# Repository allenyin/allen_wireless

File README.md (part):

**Wireless Neural Recording System**

* [Overview](#Overview)
* [Hardware](#Hardware)
	* [Steps to convert old KiCad design files](#convertKiCad)
	* [Bridge](#Bridge-hw)
	* [Headstages](#headstages)
* [Firmware](#Firmware)
	* [Dependency](#Firmware-dependency)
	* [Bridge](#Bridge-fw)
	* [RHA-headstage](#RHA-fw)
	* [RHD-headstage](#RHD-fw)
		* [Firmware versions](#firmware-versions)
		* [JTAG testing](#JTAG-testing)
		* [Utility Programs](#Utility-programs)
* [Client Software](#gtkclient)
	* [Dependency](#gtkclient-dependency)
	* [Compilation](#gtkclient-compile)
    * [Running gtkclient](#running-gtkclient)
        * [RHA-headstage gtkclient](#RHAgtkclient)
        * [RHD-headstage gtkclient](#RHDgtkclient)
        * [Spike sorting](#SpikeSorting)
        * [Saving recordings](#SavingRecordings)
        * [Test recording](#TestRecording)
        * [Configuration files](#gtkclientConfigurations)
	* [TODO/possible improvements](#gtkclient-TODO)
* [Quick Start](#quickstart)

## <a name="Overview">Overview</a>
This project is modified from the multi-branch of the wireless neural recording system of the [myopen project](https://github.com/tlh24/myopen/tree/multi) by Tim Hanson.

As summarized in Hanson's [thesis](http://m8ta.com/tim/dissertation.pdf), the original system 

>consists of digitizing headstages, receiver/ethernet bridge, and PC client software. Each headstage has 4 32-channel Intan analog amplifiers, and ADCs to digitize the amplified signals. The amplifiers are connected to an onboard Blackfin DSP BF532 which performs automatic gain control, LMS adaptive noise cancellation, 8 poles of high and lowpass filtering, two templates comparison per channel, data compression, and pipelined radio control. The radio onboard transmits 1.3Mbps full filtered analog trace of four channels and threshold/template match for two units on all 128 channels. This is interleaved with 83kbps reception,which allows the client to edit parameters on the transceiver. The radio protocol allows any memory location to be changed on the headstage (specifically the blackfin), and the headstage streams can stream from any location in memory, with the memory address set by the PC client.

[32-channel Intan analog amplifiers](http://intantech.com/products_RHA2000.html)

[Blackin DSP BF532](http://www.analog.com/en/products/processors-dsp/blackfin/adsp-bf532.html)

The bridge, which is based around [Blackfin DSP BF537](http://www.analog.com/en/products/processors-dsp/blackfin/adsp-bf537.html), collects the wirelessly transmitted data from the headstages and send them to the PC client through ethernet.

<a name="figure_overview">*System overview, from Hanson's [thesis](http://m8ta.com/tim/dissertation.pdf)*</a>

This project modified the wireless headstage by replacing each of the 4 RHA2132 amplifiers, ADCs, and power converter chips with a single [32-channel RHD2132 digitizing amplifier](http://intantech.com/products_RHD2000.html). This is to reduce the power consumption and total area of the final PCB (by about 1/3). In terms of the figure above, this is equivalent of replacing the `G=200 and 32:1 multiplexer`, `ADC` and `LDO` components in the `Digitizing headstage` blocks by one component. 

In the rest of this document, the original headstages will be refered to as **RHA-headstage**, while the new design will be referred to as **RHD-headstage**. The client software will be referred to as **gtkclient**.

This document will describe:

* The overall hardware architecture of the headstages.
* Usage and setup for the bridge, headstage, and the PC client software.
* The different firmware versions used to develop and test the RHD-headstage.
* Debugging tools.

For technical details on the implementation, development, and troubleshooting of the firmware, see Tim's thesis, and the following development notes:

1. [Wireless Headstage: Blackfin BF532 headstage firmware setup](http://allenyin.github.io/reading_list/2016/01/BlackfinSetup)
2. [Wireless Headstage: Blackfin BF532 communication with Intan RHD2132 via SPI simulation via SPORT](http://allenyin.github.io/reading_list/2015/12/Blackfin-Intan-SPORT)
3. [Wireless Headstage: AGC with Blackfin BF532 and Intan RHD2132](http://allenyin.github.io/reading_list/2015/12/WirelessAGC)
4. [Wireless Headstage: Least-Mean Squared (LMS) adaptive noise cancellation](http://allenyin.github.io/reading_list/2016/01/BlackfinLMS)
5. [Wireless Headstage: Implementing direct-form I biquad IIR filters](http://allenyin.github.io/reading_list/2016/01/DirectFormI-IIR-butterworth-filters)
6. [Wireless Headstage: Generate oscillations by setting IIR coefficients](http://allenyin.github.io/reading_list/2016/01/IIRoscillator)
7. [Spike sorting via PCA and spike detection with SAA](http://allenyin.github.io/reading_list/2016/01/BlackfinSpikeSorting)
8. [Wireless Headstage: Radio transmission protocol between headstage and gtkclient](http://allenyin.github.io/reading_list/2016/01/BlackfinRadioTrans)
9. [Wireless Headstage: gtkclient notes](http://allenyin.github.io/reading_list/2016/01/gtkclient)

This repository contains the following folders:

* `bridge_hardware`: Ported from myopen's [stage10](https://github.com/tlh24/myopen/tree/master/emg_dsp/stage10). Components  stored in `bridge_library/`. Footprint archived to `bridge_library.pretty/` to use with newer version of `kicad (Version:0.201506030104+5696~23~ubuntu14.04.1-product,release build)`.

* `headstage_hardware`: Ported from myopen's [stage9](https://github.com/tlh24/myopen/tree/master/emg_dsp/stage9). Components stored in `headstage_library/`. Footprint archived to `headstage_library.pretty/` to use with newer version of kicad.

* `headstage2_hardware`: Modified from myopen's [stage9](https://github.com/tlh24/myopen/tree/master/emg_dsp/stage9). Uses 4xRHD2132 amplifiers rather than 4xRHA2132 amplifiers front-end. Eliminated separate ADCs and analog power-supply components.

* `myopen_multi`: Firmware and gtkclient software, which includes:
    * `bridge_firmware`: Same as myopen's [firmware_stage7](https://github.com/tlh24/myopen/tree/mutli/firmware_stage7).
    * `headstage_firmware`: Firmware for RHA-headstage. Port from myopen's [firmware_stage9_tmpl](https://github.com/tlh24/myopen/tree/multi/firmware_stage9_tmpl). Uses templates matching to transmit spike timings from the headstage.
    * `headstage2_firmware`: Firmware, development and debugging files for RHD-headstage.
    * `gtkclient_multi`: gtkclient source code adapted from myopen. Makefile modified to compile on Ubuntu14.04 and to support working with RHD-headstage's firmware.
    * `flasher`: Code used to write to the flash memories of the bridge and headstage through the parallel port.
    * `common_bfin`: Code common to all firmware and gtkclient.
    * `common_host`: Code common to the bridge firmware and gtkclient.
    * `algs`: Utilities need by gtkclient.
    
---
## <a name="Hardware">Hardware</a>

## <a name="convertKiCad">Steps to convert old KiCad design files</a>
The bridge and RHA-headstage PCB were designed with Tim's [kicadocaml](https://github.com/tlh24/kicadocaml), a variant of the opensource [KiCad](http://kicad-pcb.org/) PCB cad program. The design files were ported to KiCad, however the recent changes in KiCad's EESchema introduces some problems in using projects created with older version out of the box. Those impacts include:

0. Updated device library. The new device library footprints are smaller, this can cause older schematics to be displayed with broken connections. Solution: follow the procedures outlined [here](https://lists.launchpad.net/kicad-developers/msg17639.html) to use the rescue-lib.
0. Saving the old .brd files will convert them to .kicad_pcb. Subsequent openning of the board files will then result in parse errors and no board. Solution: Never save!!! (have not yet found a good solution).

In general, the KiCad files in `bridge_hardware/` and `headstage_hardware/` are for reference only, no save/modification should be needed.

The following steps were used to convert the old project files (example using `headstage_hardware/`):

0. Extract stage9 from `/emg_dsp`.
0. Create component and footprint library folders. `cd headstage_hardware; mkdir headstage_library headstage_library.pretty`
0. Open the schematic file, press OK for the rescue components dialog. Copy the cached component to our newly created library: `cp stage9-cache.lib headstage_library/headstage.lib`
0. Go to *Preferences*->*Component Libraries* and add headstage as an active library.
0. Ctrl-E on any of the component to open library editor. Set active library to be *headstage* and save component.
0. Close schematic and open again. Now editing any of the components in the library editor should show the active library as *headstage.lib*
0.  **Important! When closing the schematic, do not click on save!**
0. Open the .brd file, click ok on the resulting dialog.
0. Ctrl-E on any of the footprint to open the footprint editor. Click on *Create new library and save footprint* from the menu bar, and select the *headstage_library.pretty* folder to store the new library.
0. Go to *Preferences*->*Footprint libraries Wizard*->*Files on my computer* and select the *headstage_library.pretty* folder. This will add that directory to the footpring libraries available in this project. Make sure to select avaliable to project only.
0. *Select active library* in the footprint editor and make it *headstage_library.pretty*.
0. Close footprint editor and go back to the board. Go to *file*->*Archive Footprints*->*Create footprint archive* and select *headstage_library.pretty* as the library. Click yes to replace library. Now *headstage_library.pretty/* contains all the footprint used in the board as .mod files.
0. Make sure when footprint editor is opened, the active library is set correctly to the one we just created.
0. Again remeber to **NOT save the board file!!**
0. Open the schematic file and run Cvpcb to associate the components and the footprints in our own custom libraries. It's possible that a footprint is found in multiple libraries, chose to associate with the ones in *headstage*.

## <a name="Bridge-hw">Bridge</a>
As illustrated by the [Receiver block in the system overview](#figure_overview), the bridge mainly consists of three antenna-2.4GHz radio pairs for wireless communication, Blackfin DSP for processing, Ethernet/MAC chip for communication with gtkclient, and DAC (typo of DAC in Tim's thesis) for outputting received neural signals as audio.

In addition to wireless communication with the headstages, the bridge is also needed to program and debug the headstages.

<a name="bridge_labeled">*Bridge Board* </a>

In the above image:

A. Power switch.

B. USB power cable. 

C. Ethernet cable. Each operating headstage requires a bridge, requiring the PC on which gtkclient operates on to be connected to multiple bridges. Therefore, the ethernet port of the bridges and the client PC should all connect to the same switch or router.

D. Audio jack. When gtkclient is running, connecting the bridge to an audio device allows the user to hear the the 4 selected channels in gtkclient.

E. Blackfin BF537 DSP processor.

F. JTAG header pins for debugging the bridge. The pin missing on the top row ensures correct orientation of the JTAG in-circuit emulator (ICE).

G. Header pins for writing firmware to the bridge's flash memory. See [bridge flashing instructions](#Bridge-fw).

H. Indicator LED lights. After power on, these LEDs would fluctuate. Normal operation is indicated by the LEDs lit up in the image lighting up. Except for the bottom most one, which should be blinking periodically.

I. Header pins for writing firmware to the headstage's flash memory. See [RHA-flashing instructions](#RHA-fw) and [RHD-flashing instructions](#RHD-fw).

J. Omnetics connector for writing firmware to the headstage's flash memory. The signals applied to the column of header pins above it are applied to the headstage through this connection to the corresponding omnetics connector on the headstage.

K. JTAG header pins for debugging the headstage. The pin missing on the left column ensures correct orientation of JTAG ICE. See [RHD firmware testing](#JTAG-testing).

L. Omnetics connector for JTAG debugging the headstage. The signals applied to the JTAG header pins are passed to the headstage through this connection.

M. 2.4GHz Nordic radio and antenna pairs. Having three antenna allow for spatial reception diversity and enable better wireless signal quality.

**Parallel Port Flash Cable**

A 25-pins [IBM PC-comptabile parallel port](https://en.wikipedia.org/wiki/Parallel_port#Pinouts) cable is modified to use for the flashing process, see [firmware section](#Firmware) for instructions.  The unmodified end of the DB25 cable is connected to the parallel port, while the modified end connects to the 7-pin header connectors on the bridge, labeled G and I above.

The flash cable on one end needs to be modified as shown below:

<a name="flash_cable">*Flash Cable Schematic*</a>

The left box shows the relevant pins on the unmodified DB25 connector, the right box shows the corresponding header pins on the bridge. There needs to be a `33pF` capacitor connecting `pin23` and `pin4` of the parallel cable. `pin5` of the cable needs to connect to the base of an NPN transistor, whose emmiter is connected to ground via either `pin23` or `pin24`, while the collector goes to `pin7` of the bridge headers.

Specifically, the parallel port to SPI correspondence is:

* `pin2` = `_CS` -- chip select of the SPI flash memory.
* `pin13` = `SO` -- the input of the parallel port is connected to the output (SO) of the flash memory.
* `pin3` = `SI` -- the output of the parallel port is connected to the input (SI) of the flash memory.
* `pin4` = `SCLK` -- serial clock (SCLK) of the flash memory.

`pin5` is not part of the 4-line SPI interface, but it is used to allow the line-driver onboard the bridge to select the flash memory to use the SPI bus. This is necessary since the SPI bus on the Blackfins of both the bridge and headstage is shared between the flash memory and the radio chip.

The modified flash cable will include the capacitor and the NPN transistor. The polarity of the 7-pin connector can be figured out by probing to see which pin is grounded onboard the bridge.

## <a name="headstages">Headstages</a>

In image below, the fully assembled RHA-headstage is on the left. The RHD-headstage is on the right.

<a name="headstages_labeled">*Headstage PCBs*</a>

Labeled in the image are the connectors the headstages can make:

A. RHA-headstage Omnetics connectors to electrodes. Each of the four connectors has two rows of 20 pins each. The leftmost and rightmost pins of each row are guide posts and connect no signals. The second leftmost and the second rightmost pins of each row are the reference electrodes.

B. RHA-headstage power connection to 3.7V battery.

C. RHA-headstage Omnetics connector for flashing memory. The JTAG debugging connector is on the back side of the board at the same location.

D. RHD-headstage Omnetics connectors to electrodes. Exactly the same as the RHA-headstage.

E. RHD-headstage power connection to 3.7V battery. Connection not installed in the pictre.

F. RHD-headstage Omnetics connector for flashing memory. The JTAG debugging connector is on the back side of the board at the same location.

The bottom half of both headstages are the `digitizing headstages` block in the [System overview diagram](#figure_overview), which is where the headstages differ hardware-wise. The top halves are the `transceiver block` and are identical.

While the electrodes for both headstages are identical, the electrode-to-amplifier connections are different. Below are the electrode-to-channel mapping for each headstage, containing only the 32 signal-carrying electrodes of the connector (excluding the guide posts). Note that each amplifier is connected to one group of 32 electrodes.

*RHA-headstage electrode-to-channel mapping, ordered from left-to-right*

top-row|31|30|29|28|27|26|25|24|23|22|21|20|19|18|17|16|
-------|---|---|---|---|---|---|---|---|---|---|---|---|---|---|---|---|
bot-row|15|14|13|12|11|10| 9| 8| 7| 6| 5| 4| 3| 2| 1| 0|

*RHD-headstage electrode-to-channel mapping, ordered from left-to-right*

top-row|23|22|21|20|19|18|17|16|15|14|13|12|11|10|9|8|
-------|---|---|---|---|---|---|---|---|---|---|---|---|---|---|---|---|
bot-row|24|25|26|27|28|29|30|31|0|1|2|3|4|5|6|7|

## <a name="Firmware">Firmware</a>
The firmware is written in a combination of C and Blackfin assembly language. While Analog Devices (ADI) provides its own software development toolchains, it requires purchasing a pretty expensive license (though it comes with a lot more support). For the myopen and this project, the open source gnu gcc blackfin toolchain is used. Further, all development was done on debian based OS. The Makefiles in this repository are tested only in Ubuntu 14.04. Minor adjustments might be needed to work on other debian-based OS.

## <a name="Firmware-dependency">Dependency</a>

Compiling the firmware requires the [Blackfin Toolchain in Linux for Bare Metal](https://blackfin.uclinux.org/doku.php?id=toolchain:installing). For debian-based linux OS:

* Download the latest version, as of June, 2015, it's `blackfin-toolchain-elf-gcc-4.3-2014R1-RC2.x86_64.tar.bz2`
* Extract and move to `/opt`
* Add path to `/opt/uClinux/bfin-elf/bin` to the `PATH` variable through `.bashrc`

Two must-have references to understand Blackfin architecture:

* [ADSP-BF5xx/ADSP-BF60x Blackfin Processor Programming Reference](http://www.analog.com/media/en/dsp-documentation/processor-manuals/Blackfin_pgr_rev2.2.pdf), describes all assembly commands and options.
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
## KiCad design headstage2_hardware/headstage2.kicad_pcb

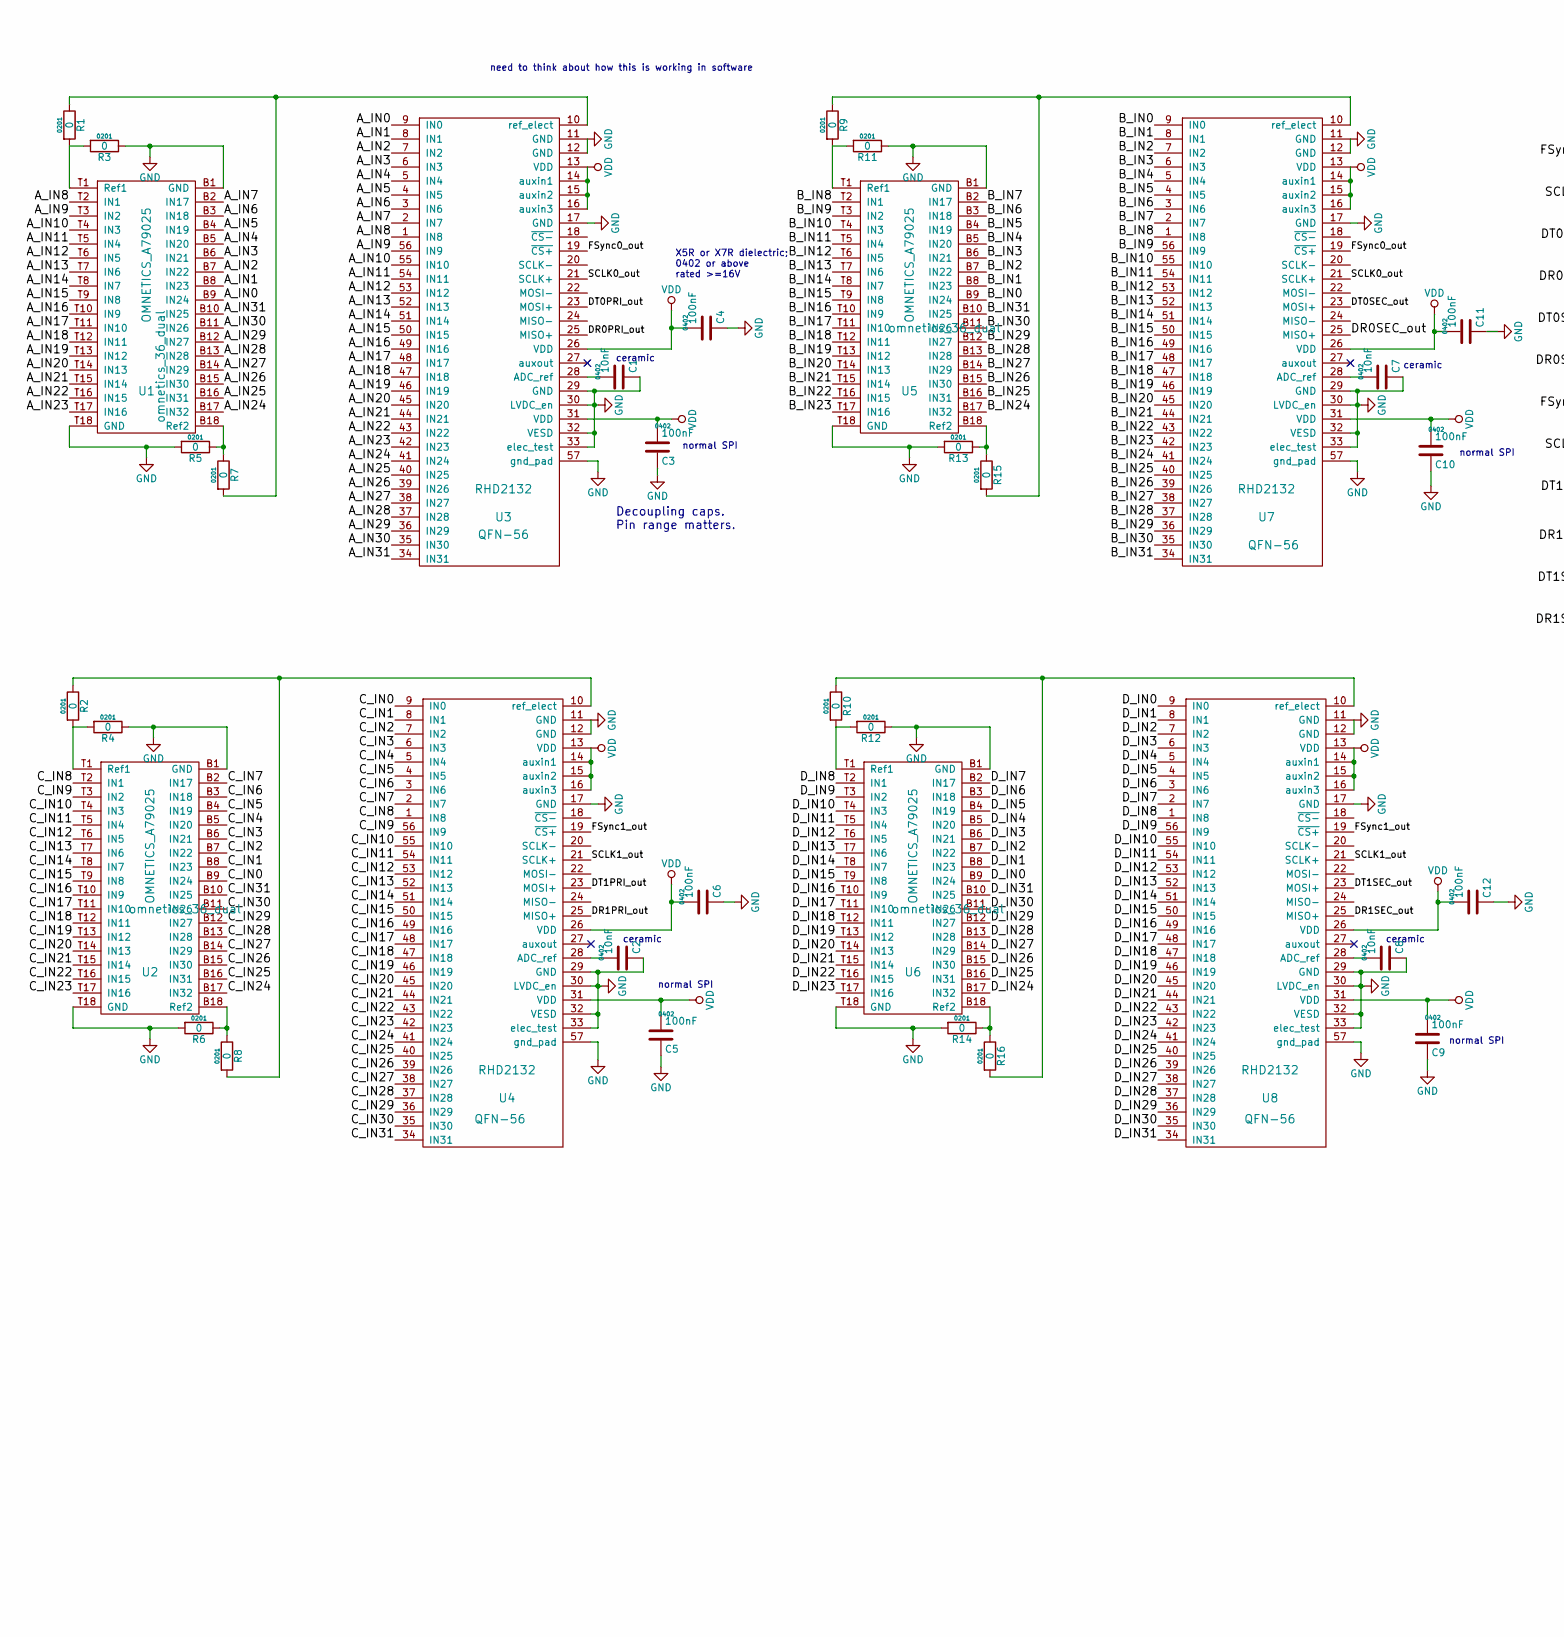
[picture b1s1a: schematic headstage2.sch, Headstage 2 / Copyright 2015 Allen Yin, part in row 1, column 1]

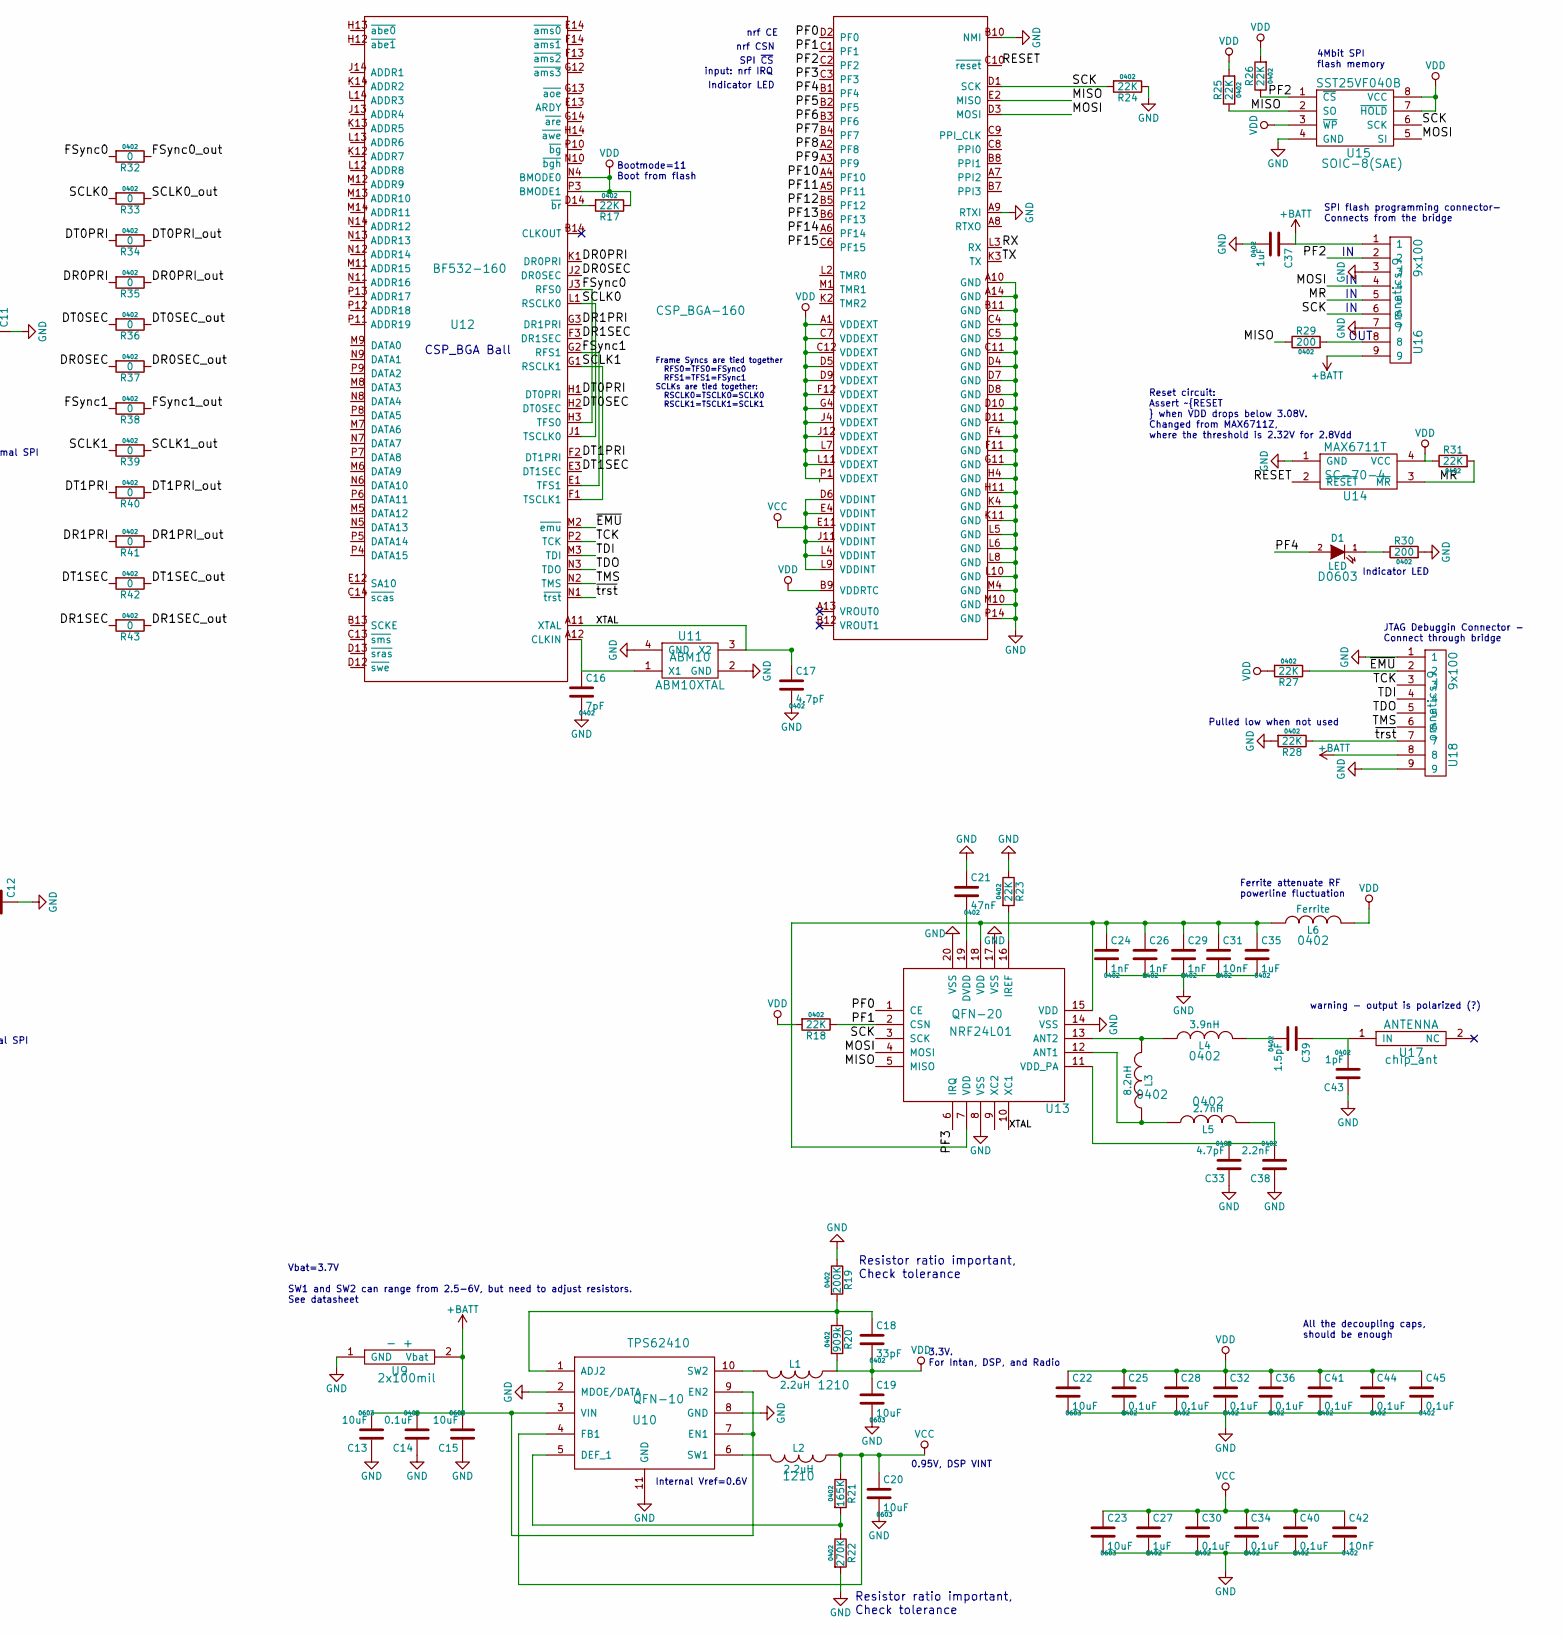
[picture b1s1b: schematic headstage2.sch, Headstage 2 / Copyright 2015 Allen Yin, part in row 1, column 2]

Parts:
C1, C2, C7, C8, C31, C42: 10nF; 0402
C3, C5, C9, C10: 100nF; 0402
C4, C6, C11, C12: 100nF; 0402; Tolerance 16V
C13, C15, C19, C20, C22, C23: 10uF; 0603
C14, C25, C28, C30, C32, C34, C36, C40, C41, C44, C45: 0.1uF; 0402
C16: 7pF; 0402
C17, C33: 4.7pF; 0402
C18: 33pF; 0402
C21: 47nF; 0402
C24, C26, C29: 1nF; 0402
C27, C35, C37: 1uF; 0402
C38: 2.2nF; 0402
C39: 1.5pF; 0402
C43: 1pF; 0402
D1: LED; D0603
L1, L2: 2.2uH; 1210
L3: 8.2nH; 0402
L4: 3.9nH; 0402
L5: 2.7nH; 0402
L6: Ferrite; 0402
R1, R2, R3, R4, R5, R6, R7, R8, R9, R10, R11, R12, R13, R14, R15, R16: 0; 0201
R17, R18, R23, R24, R25, R26, R27, R28, R31: 22K; 0402
R19: 200K; 0402
R20: 909k; 0402
R21: 165K; 0402
R22: 270K; 0402
R29, R30: 200; 0402
R32, R33, R34, R35, R36, R37, R38, R39, R40, R41, R42, R43: 0; 0402
U1, U2, U5, U6: OMNETICS_A79025; omnetics_36_dual
U3, U4, U7, U8: RHD2132; QFN-56
U9: - +; 2x100mil
U10: TPS62410; QFN-10
U11: ABM10XTAL; ABM10
U12: BF532-160; CSP_BGA-160
U13: NRF24L01; QFN-20
U14: MAX6711T; SC-70-4
U15: SST25VF040B; SOIC-8(SAE)
U16, U18: 9x100; omnetics_9
U17: ANTENNA; chip_ant

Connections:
+BATT: C13.2, C14.2, C15.2, C37.1, U9.2 (Vbat), U10.3 (VIN), U10.7 (EN1), U10.9 (EN2), U16.1, U16.9, U18.8
/A_IN0: U1.B9 (IN24), U3.9 (IN0)
/A_IN1: U1.B8 (IN23), U3.8 (IN1)
/A_IN2: U1.B7 (IN22), U3.7 (IN2)
/A_IN3: U1.B6 (IN21), U3.6 (IN3)
/A_IN4: U1.B5 (IN20), U3.5 (IN4)
/A_IN5: U1.B4 (IN19), U3.4 (IN5)
/A_IN6: U1.B3 (IN18), U3.3 (IN6)
/A_IN7: U1.B2 (IN17), U3.2 (IN7)
/A_IN8: U1.T2 (IN1), U3.1 (IN8)
/A_IN9: U1.T3 (IN2), U3.56 (IN9)
/A_IN10: U1.T4 (IN3), U3.55 (IN10)
/A_IN11: U1.T5 (IN4), U3.54 (IN11)
/A_IN12: U1.T6 (IN5), U3.53 (IN12)
/A_IN13: U1.T7 (IN6), U3.52 (IN13)
/A_IN14: U1.T8 (IN7), U3.51 (IN14)
/A_IN15: U1.T9 (IN8), U3.50 (IN15)
/A_IN16: U1.T10 (IN9), U3.49 (IN16)
/A_IN17: U1.T11 (IN10), U3.48 (IN17)
/A_IN18: U1.T12 (IN11), U3.47 (IN18)
/A_IN19: U1.T13 (IN12), U3.46 (IN19)
/A_IN20: U1.T14 (IN13), U3.45 (IN20)
/A_IN21: U1.T15 (IN14), U3.44 (IN21)
/A_IN22: U1.T16 (IN15), U3.43 (IN22)
/A_IN23: U1.T17 (IN16), U3.42 (IN23)
/A_IN24: U1.B17 (IN32), U3.41 (IN24)
/A_IN25: U1.B16 (IN31), U3.40 (IN25)
/A_IN26: U1.B15 (IN30), U3.39 (IN26)
/A_IN27: U1.B14 (IN29), U3.38 (IN27)
/A_IN28: U1.B13 (IN28), U3.37 (IN28)
/A_IN29: U1.B12 (IN27), U3.36 (IN29)
/A_IN30: U1.B11 (IN26), U3.35 (IN30)
/A_IN31: U1.B10 (IN25), U3.34 (IN31)
/B_IN0: U5.B9 (IN24), U7.9 (IN0)
/B_IN1: U5.B8 (IN23), U7.8 (IN1)
/B_IN2: U5.B7 (IN22), U7.7 (IN2)
/B_IN3: U5.B6 (IN21), U7.6 (IN3)
/B_IN4: U5.B5 (IN20), U7.5 (IN4)
/B_IN5: U5.B4 (IN19), U7.4 (IN5)
/B_IN6: U5.B3 (IN18), U7.3 (IN6)
/B_IN7: U5.B2 (IN17), U7.2 (IN7)
/B_IN8: U5.T2 (IN1), U7.1 (IN8)
/B_IN9: U5.T3 (IN2), U7.56 (IN9)
/B_IN10: U5.T4 (IN3), U7.55 (IN10)
/B_IN11: U5.T5 (IN4), U7.54 (IN11)
/B_IN12: U5.T6 (IN5), U7.53 (IN12)
/B_IN13: U5.T7 (IN6), U7.52 (IN13)
/B_IN14: U5.T8 (IN7), U7.51 (IN14)
/B_IN15: U5.T9 (IN8), U7.50 (IN15)
/B_IN16: U5.T10 (IN9), U7.49 (IN16)
/B_IN17: U5.T11 (IN10), U7.48 (IN17)
/B_IN18: U5.T12 (IN11), U7.47 (IN18)
/B_IN19: U5.T13 (IN12), U7.46 (IN19)
/B_IN20: U5.T14 (IN13), U7.45 (IN20)
/B_IN21: U5.T15 (IN14), U7.44 (IN21)
/B_IN22: U5.T16 (IN15), U7.43 (IN22)
/B_IN23: U5.T17 (IN16), U7.42 (IN23)
/B_IN24: U5.B17 (IN32), U7.41 (IN24)
/B_IN25: U5.B16 (IN31), U7.40 (IN25)
/B_IN26: U5.B15 (IN30), U7.39 (IN26)
/B_IN27: U5.B14 (IN29), U7.38 (IN27)
/B_IN28: U5.B13 (IN28), U7.37 (IN28)
/B_IN29: U5.B12 (IN27), U7.36 (IN29)
/B_IN30: U5.B11 (IN26), U7.35 (IN30)
/B_IN31: U5.B10 (IN25), U7.34 (IN31)
/C_IN0: U2.B9 (IN24), U4.9 (IN0)
/C_IN1: U2.B8 (IN23), U4.8 (IN1)
/C_IN2: U2.B7 (IN22), U4.7 (IN2)
/C_IN3: U2.B6 (IN21), U4.6 (IN3)
/C_IN4: U2.B5 (IN20), U4.5 (IN4)
/C_IN5: U2.B4 (IN19), U4.4 (IN5)
/C_IN6: U2.B3 (IN18), U4.3 (IN6)
/C_IN7: U2.B2 (IN17), U4.2 (IN7)
/C_IN8: U2.T2 (IN1), U4.1 (IN8)
/C_IN9: U2.T3 (IN2), U4.56 (IN9)
/C_IN10: U2.T4 (IN3), U4.55 (IN10)
/C_IN11: U2.T5 (IN4), U4.54 (IN11)
/C_IN12: U2.T6 (IN5), U4.53 (IN12)
/C_IN13: U2.T7 (IN6), U4.52 (IN13)
/C_IN14: U2.T8 (IN7), U4.51 (IN14)
/C_IN15: U2.T9 (IN8), U4.50 (IN15)
/C_IN16: U2.T10 (IN9), U4.49 (IN16)
/C_IN17: U2.T11 (IN10), U4.48 (IN17)
/C_IN18: U2.T12 (IN11), U4.47 (IN18)
/C_IN19: U2.T13 (IN12), U4.46 (IN19)
/C_IN20: U2.T14 (IN13), U4.45 (IN20)
/C_IN21: U2.T15 (IN14), U4.44 (IN21)
/C_IN22: U2.T16 (IN15), U4.43 (IN22)
/C_IN23: U2.T17 (IN16), U4.42 (IN23)
/C_IN24: U2.B17 (IN32), U4.41 (IN24)
/C_IN25: U2.B16 (IN31), U4.40 (IN25)
/C_IN26: U2.B15 (IN30), U4.39 (IN26)
/C_IN27: U2.B14 (IN29), U4.38 (IN27)
/C_IN28: U2.B13 (IN28), U4.37 (IN28)
/C_IN29: U2.B12 (IN27), U4.36 (IN29)
/C_IN30: U2.B11 (IN26), U4.35 (IN30)
/C_IN31: U2.B10 (IN25), U4.34 (IN31)
/DR0PRI: R35.2, U12.K1 (DR0PRI)
/DR0PRI_out: R35.1, U3.25 (MISO+)
/DR0SEC: R37.2, U12.J2 (DR0SEC)
/DR0SEC_out: R37.1, U7.25 (MISO+)
/DR1PRI: R41.2, U12.G3 (DR1PRI)
/DR1PRI_out: R41.1, U4.25 (MISO+)
/DR1SEC: R43.2, U12.F3 (DR1SEC)
/DR1SEC_out: R43.1, U8.25 (MISO+)
/DT0PRI: R34.2, U12.H1 (DT0PRI)
/DT0PRI_out: R34.1, U3.23 (MOSI+)
/DT0SEC: R36.2, U12.H2 (DT0SEC)
/DT0SEC_out: R36.1, U7.23 (MOSI+)
/DT1PRI: R40.2, U12.F2 (DT1PRI)
/DT1PRI_out: R40.1, U4.23 (MOSI+)
/DT1SEC: R42.2, U12.E3 (DT1SEC)
/DT1SEC_out: R42.1, U8.23 (MOSI+)
/D_IN0: U6.B9 (IN24), U8.9 (IN0)
/D_IN1: U6.B8 (IN23), U8.8 (IN1)
/D_IN2: U6.B7 (IN22), U8.7 (IN2)
/D_IN3: U6.B6 (IN21), U8.6 (IN3)
/D_IN4: U6.B5 (IN20), U8.5 (IN4)
/D_IN5: U6.B4 (IN19), U8.4 (IN5)
/D_IN6: U6.B3 (IN18), U8.3 (IN6)
/D_IN7: U6.B2 (IN17), U8.2 (IN7)
/D_IN8: U6.T2 (IN1), U8.1 (IN8)
/D_IN9: U6.T3 (IN2), U8.56 (IN9)
/D_IN10: U6.T4 (IN3), U8.55 (IN10)
/D_IN11: U6.T5 (IN4), U8.54 (IN11)
/D_IN12: U6.T6 (IN5), U8.53 (IN12)
/D_IN13: U6.T7 (IN6), U8.52 (IN13)
/D_IN14: U6.T8 (IN7), U8.51 (IN14)
/D_IN15: U6.T9 (IN8), U8.50 (IN15)
/D_IN16: U6.T10 (IN9), U8.49 (IN16)
/D_IN17: U6.T11 (IN10), U8.48 (IN17)
/D_IN18: U6.T12 (IN11), U8.47 (IN18)
/D_IN19: U6.T13 (IN12), U8.46 (IN19)
/D_IN20: U6.T14 (IN13), U8.45 (IN20)
/D_IN21: U6.T15 (IN14), U8.44 (IN21)
/D_IN22: U6.T16 (IN15), U8.43 (IN22)
/D_IN23: U6.T17 (IN16), U8.42 (IN23)
/D_IN24: U6.B17 (IN32), U8.41 (IN24)
/D_IN25: U6.B16 (IN31), U8.40 (IN25)
/D_IN26: U6.B15 (IN30), U8.39 (IN26)
/D_IN27: U6.B14 (IN29), U8.38 (IN27)
/D_IN28: U6.B13 (IN28), U8.37 (IN28)
/D_IN29: U6.B12 (IN27), U8.36 (IN29)
/D_IN30: U6.B11 (IN26), U8.35 (IN30)
/D_IN31: U6.B10 (IN25), U8.34 (IN31)
/FSync0: R32.2, U12.H3 (TFS0), U12.J3 (RFS0)
/FSync0_out: R32.1, U3.19 (~CS+), U7.19 (~CS+)
/FSync1: R38.2, U12.E1 (TFS1), U12.G2 (RFS1)
/FSync1_out: R38.1, U4.19 (~CS+), U8.19 (~CS+)
/MISO: R25.1, R29.1, U12.E2 (MISO), U13.5 (MISO), U15.2 (SO)
/MOSI: U12.D3 (MOSI), U13.4 (MOSI), U15.5 (SI), U16.4
/MR: R31.2, U14.3 (~MR), U16.5
/PF0: U12.D2 (PF0), U13.1 (CE)
/PF1: R18.1, U12.C1 (PF1), U13.2 (CSN)
/PF2: R26.1, U12.C2 (PF2), U15.1 (~CS), U16.2
/PF3: U12.C3 (PF3), U13.6 (IRQ)
/PF4: D1.2 (A), U12.B1 (PF4)
/PF5: U12.B2 (PF5)
/PF6: U12.B3 (PF6)
/PF7: U12.B4 (PF7)
/PF8: U12.A2 (PF8)
/PF9: U12.A3 (PF9)
/PF10: U12.A4 (PF10)
/PF11: U12.A5 (PF11)
/PF12: U12.B5 (PF12)
/PF13: U12.B6 (PF13)
/PF14: U12.A6 (PF14)
/PF15: U12.C6 (PF15)
/RESET: U12.C10 (~reset), U14.2 (~RESET)
/RX: U12.L3 (RX)
/SCK: R24.2, U12.D1 (SCK), U13.3 (SCK), U15.6 (SCK), U16.6
/SCLK0: R33.2, U12.J1 (TSCLK0), U12.L1 (RSCLK0)
/SCLK0_out: R33.1, U3.21 (SCLK+), U7.21 (SCLK+)
/SCLK1: R39.2, U12.F1 (TSCLK1), U12.G1 (RSCLK1)
/SCLK1_out: R39.1, U4.21 (SCLK+), U8.21 (SCLK+)
/TCK: U12.P2 (TCK), U18.3
/TDI: U12.M3 (TDI), U18.4
/TDO: U12.N3 (TDO), U18.5
/TMS: U12.N2 (TMS), U18.6
/TX: U12.K3 (TX)
/XTAL: C17.1, U11.3 (X2), U12.A11 (XTAL), U13.10 (XC1)
/~EMU: R27.1, U12.M2 (~emu), U18.2
/~trst: R28.1, U12.N1 (~trst), U18.7
GND: C1.1, C2.1, C3.1, C4.1, C5.1, C6.1, C7.1, C8.1, C9.1, C10.1, C11.1, C12.1, C13.1, C14.1, C15.1, C16.2, C17.2, C19.2, C20.2, C21.1, C22.2, C23.2, C24.2, C25.2, C26.2, C27.2, C28.2, C29.2, C30.2, C31.2, C32.2, C33.1, C34.2, C35.2, C36.2, C37.2, C38.1, C40.2, C41.2, C42.2, C43.1, C44.2, C45.2, R3.1, R4.1, R5.2, R6.2, R11.1, R12.1, R13.2, R14.2, R19.1, R22.2, R23.1, R24.1, R28.2, R30.2, U1.B1 (GND), U1.T18 (GND), U2.B1 (GND), U2.T18 (GND), U3.11 (GND), U3.12 (GND), U3.17 (GND), U3.29 (GND), U3.30 (LVDC_en), U3.32 (VESD), U3.33 (elec_test), U3.57 (gnd_pad), U4.11 (GND), U4.12 (GND), U4.17 (GND), U4.29 (GND), U4.30 (LVDC_en), U4.32 (VESD), U4.33 (elec_test), U4.57 (gnd_pad), U5.B1 (GND), U5.T18 (GND), U6.B1 (GND), U6.T18 (GND), U7.11 (GND), U7.12 (GND), U7.17 (GND), U7.29 (GND), U7.30 (LVDC_en), U7.32 (VESD), U7.33 (elec_test), U7.57 (gnd_pad), U8.11 (GND), U8.12 (GND), U8.17 (GND), U8.29 (GND), U8.30 (LVDC_en), U8.32 (VESD), U8.33 (elec_test), U8.57 (gnd_pad), U9.1 (GND), U10.2 (MDOE/DATA), U10.8 (GND), U10.11 (GND), U11.2 (GND), U11.4 (GND), U12.A9 (RTXI), U12.A10 (GND), U12.A14 (GND), U12.B10 (NMI), U12.B11 (GND), U12.C4 (GND), U12.C5 (GND), U12.C11 (GND), U12.D4 (GND), U12.D7 (GND), U12.D8 (GND), U12.D10 (GND), U12.D11 (GND), U12.F4 (GND), U12.F11 (GND), U12.G11 (GND), U12.H4 (GND), U12.H11 (GND), U12.K4 (GND), U12.K11 (GND), U12.L5 (GND), U12.L6 (GND), U12.L8 (GND), U12.L10 (GND), U12.M4 (GND), U12.M10 (GND), U12.P14 (GND), U13.8 (VSS), U13.14 (VSS), U13.17 (VSS), U13.20 (VSS), U14.1 (GND), U15.4 (GND), U16.3, U16.7, U18.1, U18.9
unnamed: C1.2, U3.28 (ADC_ref)
unnamed: C2.2, U4.28 (ADC_ref)
unnamed: C7.2, U7.28 (ADC_ref)
unnamed: C8.2, U8.28 (ADC_ref)
unnamed: C16.1, U11.1 (X1), U12.A12 (CLKIN)
unnamed: C18.1, R19.2, R20.1, U10.1 (ADJ2)
unnamed: C21.2, U13.19 (DVDD)
unnamed: C24.1, C26.1, C29.1, C31.1, C35.1, L6.1, U13.7 (VDD), U13.15 (VDD), U13.18 (VDD)
unnamed: C33.2, C38.2, L5.2, U13.11 (VDD_PA)
unnamed: C39.1, C43.2, U17.1 (IN)
unnamed: C39.2, L4.2
unnamed: D1.1 (K), R30.1
unnamed: L1.2, U10.10 (SW2)
unnamed: L2.2, U10.6 (SW1)
unnamed: L3.1, L5.1, U13.12 (ANT1)
unnamed: L3.2, L4.1, U13.13 (ANT2)
unnamed: R1.1, R7.2, U3.10 (ref_elect)
unnamed: R1.2, R3.2, U1.T1 (Ref1)
unnamed: R2.1, R8.2, U4.10 (ref_elect)
unnamed: R2.2, R4.2, U2.T1 (Ref1)
unnamed: R5.1, R7.1, U1.B18 (Ref2)
unnamed: R6.1, R8.1, U2.B18 (Ref2)
unnamed: R10.1, R16.2, U8.10 (ref_elect)
unnamed: R10.2, R12.2, U6.T1 (Ref1)
unnamed: R9.2, R11.2, U5.T1 (Ref1)
unnamed: R13.1, R15.1, U5.B18 (Ref2)
unnamed: R14.1, R16.1, U6.B18 (Ref2)
unnamed: R9.1, R15.2, U7.10 (ref_elect)
unnamed: R17.2, U12.D14 (~br)
unnamed: R21.2, R22.1, U10.5 (DEF_1)
unnamed: R23.2, U13.16 (IREF)
unnamed: R29.2, U16.8
VCC: C20.1, C23.1, C27.1, C30.1, C34.1, C40.1, C42.1, L2.1, R21.1, U10.4 (FB1), U12.D6 (VDDINT), U12.E4 (VDDINT), U12.E11 (VDDINT), U12.J11 (VDDINT), U12.L4 (VDDINT), U12.L9 (VDDINT)
VDD: C3.2, C4.2, C5.2, C6.2, C9.2, C10.2, C11.2, C12.2, C18.2, C19.1, C22.1, C25.1, C28.1, C32.1, C36.1, C41.1, C44.1, C45.1, L1.1, L6.2, R17.1, R18.2, R20.2, R25.2, R26.2, R27.2, R31.1, U3.13 (VDD), U3.14 (auxin1), U3.15 (auxin2), U3.16 (auxin3), U3.26 (VDD), U3.31 (VDD), U4.13 (VDD), U4.14 (auxin1), U4.15 (auxin2), U4.16 (auxin3), U4.26 (VDD), U4.31 (VDD), U7.13 (VDD), U7.14 (auxin1), U7.15 (auxin2), U7.16 (auxin3), U7.26 (VDD), U7.31 (VDD), U8.13 (VDD), U8.14 (auxin1), U8.15 (auxin2), U8.16 (auxin3), U8.26 (VDD), U8.31 (VDD), U12.A1 (VDDEXT), U12.B9 (VDDRTC), U12.C7 (VDDEXT), U12.C12 (VDDEXT), U12.D5 (VDDEXT), U12.D9 (VDDEXT), U12.F12 (VDDEXT), U12.G4 (VDDEXT), U12.J4 (VDDEXT), U12.J12 (VDDEXT), U12.L7 (VDDEXT), U12.L11 (VDDEXT), U12.N4 (BMODE0), U12.P1 (VDDEXT), U12.P3 (BMODE1), U14.4 (VCC), U15.3 (~WP), U15.7 (~HOLD), U15.8 (VCC)

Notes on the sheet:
Vbat=3.7V SW1 and SW2 can range from 2.5-6V, but need to adjust resistors. See datasheet
0.95V, DSP VINT
3.3V. For Intan, DSP, and Radio
CSP_BGA Ball
Bootmode=11 Boot from flash
4Mbit SPI flash memory
Indicator LED
OUT
SPI flash programming connector- Connects from the bridge
Reset circuit: Assert ~RESET when VDD drops below 3.08V. Changed from MAX6711Z, where the threshold is 2.32V for 2.8Vdd
nrf CE
nrf CSN
SPI ~CS
input: nrf IRQ
Ferrite attenuate RF powerline fluctuation
warning - output is polarized (?)
Pulled low when not used
JTAG Debuggin Connector - Connect through bridge
All the decoupling caps, should be enough
Internal Vref=0.6V
normal SPI
ceramic
Decoupling caps. Pin range matters.
Frame Syncs are tied together RFS0=TFS0=FSync0 RFS1=TFS1=FSync1 SCLKs are tied together: RSCLK0=TSCLK0=SCLK0 RSCLK1=TSCLK1=SCLK1
need to think about how this is working in software
X5R or X7R dielectric; 0402 or above rated >=16V
Resistor ratio important, Check tolerance

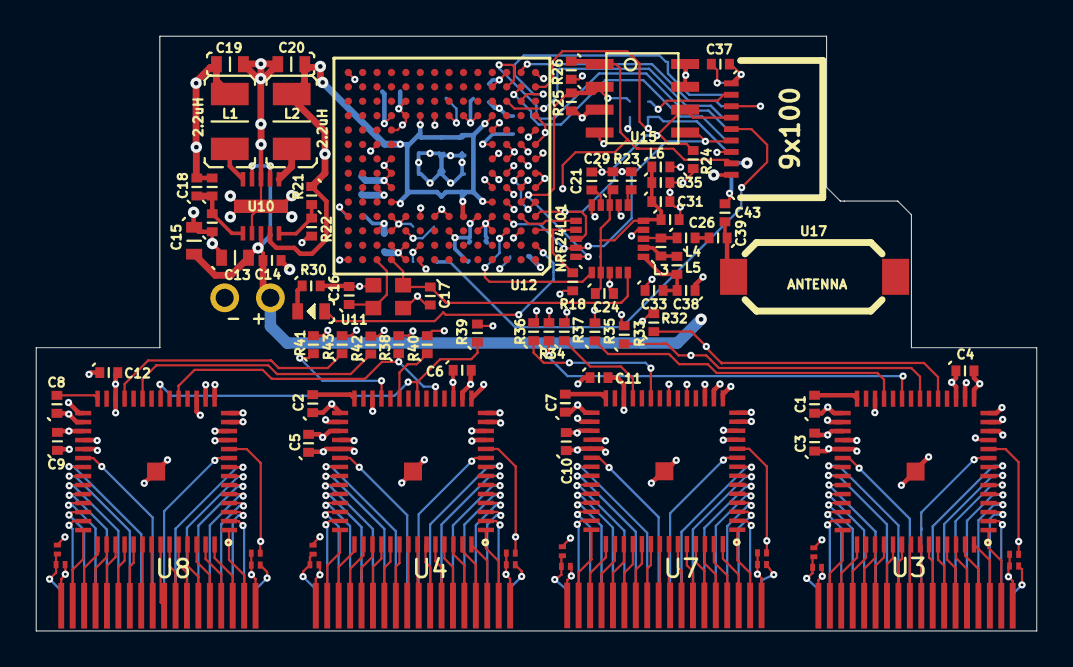
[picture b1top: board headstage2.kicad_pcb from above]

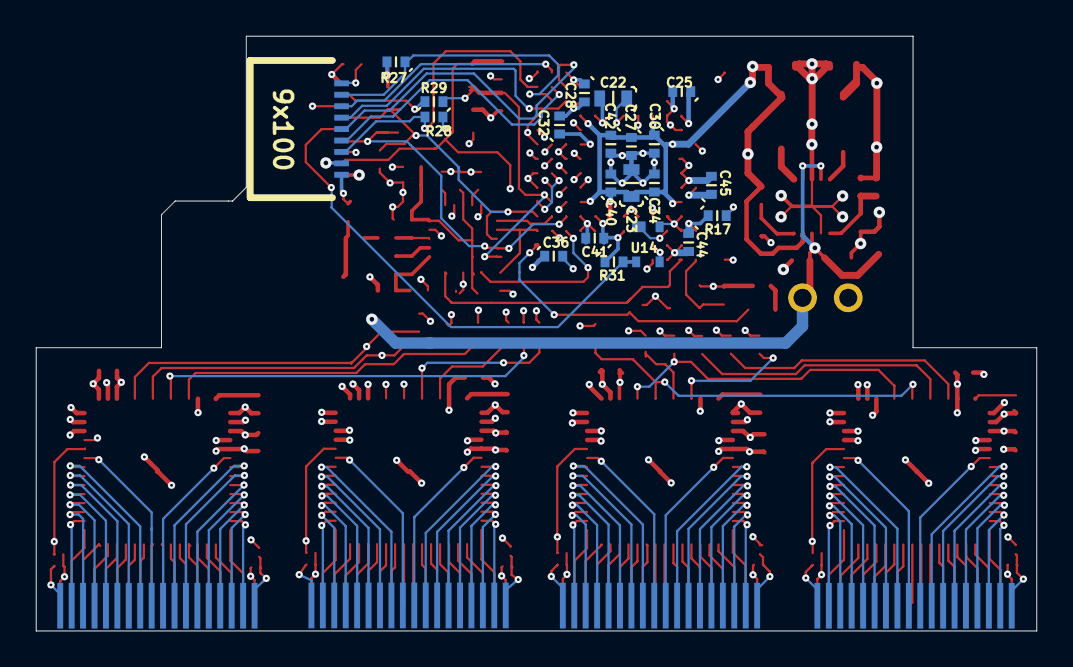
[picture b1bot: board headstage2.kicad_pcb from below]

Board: 6 copper layers, 55.6 x 33.0 mm, 113 parts (21 on the bottom side), 205 nets.

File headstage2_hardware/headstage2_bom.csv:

ITEM,REFERENCES,VALUE,FOOTPRINT,MANUFACTUER,SUPPLIER,SUPPLIER,PART,NUMBER,Notes,
1,C1,10nF,402,TDK,Mouser,810-C0402X5R0J103K,"ceramic, X5R, 6V",,,
2,C2,10nF,402,TDK,Mouser,810-C0402X5R0J103K,"ceramic, X5R, 6V",,,
3,C3,100nF,402,TDK,Mouser,810-C1005X5R1C104K,"ceramic, X5R, 16V",,,
4,C4,100nF,402,TDK,Mouser,810-C1005X5R1C104K,"ceramic, X5R, 16V",,,
5,C5,100nF,402,TDK,Mouser,810-C1005X5R1C104K,"ceramic, X5R, 16V",,,
6,C6,100nF,402,TDK,Mouser,810-C1005X5R1C104K,"ceramic, X5R, 16V",,,
7,C7,10nF,402,TDK,Mouser,810-C0402X5R0J103K,"ceramic, X5R, 6V",,,
8,C8,10nF,402,TDK,Mouser,810-C0402X5R0J103K,"ceramic, X5R, 6V",,,
9,C9,100nF,402,TDK,Mouser,810-C1005X5R1C104K,"ceramic, X5R, 16V",,,
10,C10,100nF,402,TDK,Mouser,810-C1005X5R1C104K,"ceramic, X5R, 16V",,,
11,C11,100nF,402,TDK,Mouser,810-C1005X5R1C104K,"ceramic, X5R, 16V",,,
12,C12,100nF,402,TDK,Mouser,810-C1005X5R1C104K,"ceramic, X5R, 16V",,,
13,C13,10uF,603,TDK,Mouser,810-C1608X5R1E106M,"ceramic, X5R, 25V",,,
14,C14,0.1uF,402,Murata,Mouser,81-GRM155R71C104KA88,"ceramic,X5R,10V",,,
15,C15,10uF,603,TDK,Mouser,810-C1608X5R1E106M,"ceramic, X5R, 25V",,,
16,C16,7pF,402,Murata,Mouser,81-GJM1555C1H7R0BB1D,"crystal load: high Q, low loss, +/-0.1pF",,,
17,C17,4.7pF,402,AVX,Mouser,581-04025U4R7BAT2A,"crystal load: high Q, low loss, +/-0.1pF",,,
18,C18,33pF,402,Johansson,Mouser,609-500R07S330JV4T,ceramic,,,
19,C19,10uF,603,TDK,Mouser,810-C1608X5R1E106M,"ceramic, X5R, 25V",,,
20,C20,10uF,603,TDK,Mouser,810-C1608X5R1E106M,"ceramic, X5R, 25V",,,
21,C21,47nF,402,Vishay,Mouser,77-VJ0402Y473JXQCBC,ceramic,,,
22,C22,10uF,603,TDK,Mouser,810-C1608X5R1E106M,"ceramic, X5R, 25V",,,
23,C23,10uF,603,TDK,Mouser,810-C1608X5R1E106M,"ceramic, X5R, 25V",,,
24,C24,1nF,402,Kermet,Mouser,80-C0402C102J4R,"ceramic, X7R, 16V",,,
25,C25,0.1uF,402,Murata,Mouser,81-GRM155R71C104KA88,"ceramic, X7R, 16V, 10%",,,
26,C26,1nF,402,Kermet,Mouser,80-C0402C102J4R,"ceramic, X7R, 16V",,,
27,C27,1uF,402,Murata,Mouser,81-GRM155R61E105KA2D,"ceramic, X5R, 25V, 10%",,,
28,C28,0.1uF,402,Murata,Mouser,81-GRM155R71C104KA88,"ceramic, X7R, 16V, 10%",,,
29,C29,1nF,402,Kermet,Mouser,80-C0402C102J4R,"ceramic, X7R, 16V",,,
30,C30,0.1uF,402,Murata,Mouser,81-GRM155R71C104KA88,"ceramic, X7R, 16V, 10%",,,
31,C31,10nF,402,Murata,Mouser,81-GRM36X103K25,"cermaic, X7R, 25V, 10%",,,
32,C32,"0,1uF",402,Murata,Mouser,81-GRM155R71C104KA88,"ceramic, X7R, 16V, 10%",,,
33,C33,4.7pF,402,AVX,Mouser,581-04025U4R7BAT2A,"crystal load: high Q, low loss, +/-0.1pF",,,
34,C34,0.1uF,402,Murata,Mouser,81-GRM155R71C104KA88,"ceramic, X7R, 16V, 10%",,,
35,C35,0.1uF,402,Murata,Mouser,81-GRM155R71C104KA88,"ceramic, X7R, 16V, 10%",,,
36,C36,0.1uF,402,Murata,Mouser,81-GRM155R71C104KA88,"ceramic, X7R, 16V, 10%",,,
37,C37,1uF,402,Murata,Mouser,81-GRM155R61E105KA2D,"ceramic, X5R, 25V, 10%",,,
38,C38,2.2nF,402,AVX,Mouser,581-04025C222JAT2A,"ceramic, X7R, 50V, 5%",,,
39,C39,1.5pF,402,AVX,Mouser,581-04025U1R5BAT2A,"ceramic, C0G, 50V, +/-0.1pF, RF",,,
40,C40,0.1uF,402,Murata,Mouser,81-GRM155R71C104KA88,"ceramic, X7R, 16V, 10%",,,
41,C41,0.1uF,402,Murata,Mouser,81-GRM155R71C104KA88,"ceramic, X7R, 16V, 10%",,,
42,C42,10nF,402,Murata,Mouser,81-GRM36X103K25,"cermaic, X7R, 25V, 10%",,,
43,C43,1pF,402,AVX,Mouser,581-04025U1R0BAT2A,"ceramic, C0G, 50V, +/-0.1pF, RF",,,
44,C44,0.1uF,402,Murata,Mouser,81-GRM155R71C104KA88,"ceramic, X7R, 16V, 10%",,,
45,C45,0.1uF,402,Murata,Mouser,81-GRM155R71C104KA88,"ceramic, X7R, 16V, 10%",,,
46,D1,LED,D0603?,Lumex,Mouser,696-SML-LX0603IW,"Red, 2V, 20mA, 160 view angle",,,
47,L1,2.2uH,1210,Taiyo,Yuden,Digikey,587-2165-1-ND,"1.6A rating, 150MHz resonant freq, 78 mOhm DC",,
48,L2,2.2uF,1210,Taiyo,Yuden,Digikey,587-2165-1-ND,"1.6A rating, 150MHz resonant freq, 78 mOhm DC",,
49,L3,8.2nH,402,Wurth,Digikey,732-1719-1-ND,"680mA rating, 4.4GHz resonant freq, +/-5%, 100 mOhm DC",,,
50,L4,3.9nH,402,Wurth,Digikey,732-1711-1-ND,"840mA rating, 5.8GHz resonant freq, +/-5%, 64 mOhm DC",,,
51,L5,2.7nH,402,Panasonic,Digikey,PCD1851CT-ND,"400mA rating, 5.5GHz resonant freq, +/-5%, 100 mOhm DC",,,
52,L6,Ferrite,402,Murata,Digikey,490-1006-1-ND,"300mA rating, 600 Ohm @ 100MHz, 600 mOhm DC",,,
53,R1,0,201,Panasonic,Digikey,P0.0AGCT-ND,0.05W,,,
54,R2,0,201,Panasonic,Digikey,P0.0AGCT-ND,0.05W,,,
55,R3,0,201,Panasonic,Digikey,P0.0AGCT-ND,0.05W,,,
56,R4,0,201,Panasonic,Digikey,P0.0AGCT-ND,0.05W,,,
57,R5,0,201,Panasonic,Digikey,P0.0AGCT-ND,0.05W,,,
58,R6,0,201,Panasonic,Digikey,P0.0AGCT-ND,0.05W,,,
59,R7,0,201,Panasonic,Digikey,P0.0AGCT-ND,0.05W,,,
60,R8,0,201,Panasonic,Digikey,P0.0AGCT-ND,0.05W,,,
61,R9,0,201,Panasonic,Digikey,P0.0AGCT-ND,0.05W,,,
62,R10,0,201,Panasonic,Digikey,P0.0AGCT-ND,0.05W,,,
63,R11,0,201,Panasonic,Digikey,P0.0AGCT-ND,0.05W,,,
64,R12,0,201,Panasonic,Digikey,P0.0AGCT-ND,0.05W,,,
65,R13,0,201,Panasonic,Digikey,P0.0AGCT-ND,0.05W,,,
66,R14,0,201,Panasonic,Digikey,P0.0AGCT-ND,0.05W,,,
67,R15,0,201,Panasonic,Digikey,P0.0AGCT-ND,0.05W,,,
68,R16,0,201,Panasonic,Digikey,P0.0AGCT-ND,0.05W,,,
69,R17,22K,402,Panasonic,Digikey,P22.0KLCT-ND,"Thick film, +/-1%, 0.1W",,,
70,R18,22K,402,Panasonic,Digikey,P22.0KLCT-ND,"Thick film, +/-1%, 0.1W",,,
71,R19,200K,402,Panasonic,Digikey,P200KJCT-ND,"Thick film, +/-1%, 0.1W",,,
72,R20,909K,402,Panasonic,Digikey,P909KLCT-ND,"Thick film, +/-1%, 0.1W",,,
73,R21,165K,402,Panasonic,Digikey,P165KLCT-ND,"Thick film, +/-1%, 0.1W",,,
74,R22,270K,402,Panasonic,Digikey,P270KLCT-ND,"Thick film, +/-1%, 0.1W",,,
75,R23,22K,402,Panasonic,Digikey,P22.0KLCT-ND,"Thick film, +/-1%, 0.1W",,,
76,R24,22K,402,Panasonic,Digikey,P22.0KLCT-ND,"Thick film, +/-1%, 0.1W",,,
77,R25,22K,402,Panasonic,Digikey,P22.0KLCT-ND,"Thick film, +/-1%, 0.1W",,,
78,R26,22K,402,Panasonic,Digikey,P22.0KLCT-ND,"Thick film, +/-1%, 0.1W",,,
79,R27,22K,402,Panasonic,Digikey,P22.0KLCT-ND,"Thick film, +/-1%, 0.1W",,,
80,R28,22K,402,Panasonic,Digikey,P22.0KLCT-ND,"Thick film, +/-1%, 0.1W",,,
81,R29,200K,402,Panasonic,Digikey,P200KLCT-ND,"Thick film, +/-1%, 0.1W",,,
82,R30,200,402,Panasonic,Digikey,P200JCT-ND,"Thick film, +/-5%, 0.1W",,,
83,R31,22K,402,Panasonic,Digikey,P22.0KLCT-ND,"Thick film, +/-1%, 0.1W",,,
84,R32,0,402,Panasonic,Digikey,P0.0JTR-ND,0.1W,,,
85,R33,0,402,Panasonic,Digikey,P0.0JTR-ND,0.1W,,,
86,R34,0,402,Panasonic,Digikey,P0.0JTR-ND,0.1W,,,
87,R35,0,402,Panasonic,Digikey,P0.0JTR-ND,0.1W,,,
88,R36,0,402,Panasonic,Digikey,P0.0JTR-ND,0.1W,,,
89,R37,0,402,Panasonic,Digikey,P0.0JTR-ND,0.1W,,,
90,R38,0,402,Panasonic,Digikey,P0.0JTR-ND,0.1W,,,
91,R39,0,402,Panasonic,Digikey,P0.0JTR-ND,0.1W,,,
92,R40,0,402,Panasonic,Digikey,P0.0JTR-ND,0.1W,,,
93,R41,0,402,Panasonic,Digikey,P0.0JTR-ND,0.1W,,,
94,R42,0,402,Panasonic,Digikey,P0.0JTR-ND,0.1W,,,
95,R43,0,402,Panasonic,Digikey,P0.0JTR-ND,0.1W,,,
96,U1,OMNETICS-36-Dual,OMNETICS-36-Dual,Omnetics,,A79025-001,,,,
97,U2,OMNETICS-36-Dual,OMNETICS-36-Dual,Omnetics,,A79025-001,,,,
98,U3,RHD2132,QFN-56,Intan,Tech,,D8214,,,
99,U4,RHD2132,QFN-56,Intan,Tech,,D8214,,,
100,U5,OMNETICS-36-Dual,OMNETICS-36-Dual,Omnetics,,A79025-001,,,,
101,U6,OMNETICS-36-Dual,OMNETICS-36-Dual,Omnetics,,A79025-001,,,,
102,U7,RHD2132,QFN-56,Intan,Tech,,D8214,,,
103,U8,RHD2132,QFN-56,Intan,Tech,,D8214,,,
104,U9,-/+,2x100mil,,,,,,,
105,U10,TPS62410DRCR,QFN-10,Texas,Instrument,Digikey,296-25488-1-ND,,,
106,U11,ABM10XTAL,ABM10,Abracon,Digikey,535-10923-1-ND,"16MHz+/-20ppm, 30ppm stability, 150 Ohm ESR",,,
107,U12,BF532-160,CSP_BGA160,Analog,Devices,Digikey,ADSP-BF532SBBCZ400-ND,400MHz,,
108,U13,NRF24L01,QFN-20,Nordic,Semi,Mouser,949-NRF24L01P-R,,,
109,U14,MAX6711T,SC-70-4,Maxim,Digikey,MAX6711TEXS+TCT-ND,Threshold,Voltage,=,3.08V
110,U15,SST25VF040B-80-4I-SAE,SOIC-8,Microchip,Mouser,804-25VF040B8ISAE,,,,
111,U16,OMNETICS-9x100,OMNETICS-9x100,,,,,,,
112,U17,Multilayer Chip antenna,748891025,Wurth,Digikey,732-1838-1-ND,2.4-2.5GHz; VSWR=2; Gain=3dB; Marked spot toward board,,,
113,U18,OMNETICS-9x100,OMNETICS-9x100,,,,,,,

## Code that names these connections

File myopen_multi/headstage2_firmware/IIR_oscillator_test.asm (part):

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
    /* PF pin setup:
       Make sure we aren't driving anything we need not be.
       - SPI_CE = PF0  -- initially high to deselect - Output - radio
       - SPI_CSN = PF1 -- initially high to deselect - Output - radio
       - LED_BLINK = PF4 -- initially high to light LED - Output

       - SPI_CS = PF2  -- flash memory - input
       - SPI_IRQ = PF3 -- radio IRQ    - input

       FIO_DIR = 0b 0000 0000 0001 0011  (1 = output, 0 = input)
    */
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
